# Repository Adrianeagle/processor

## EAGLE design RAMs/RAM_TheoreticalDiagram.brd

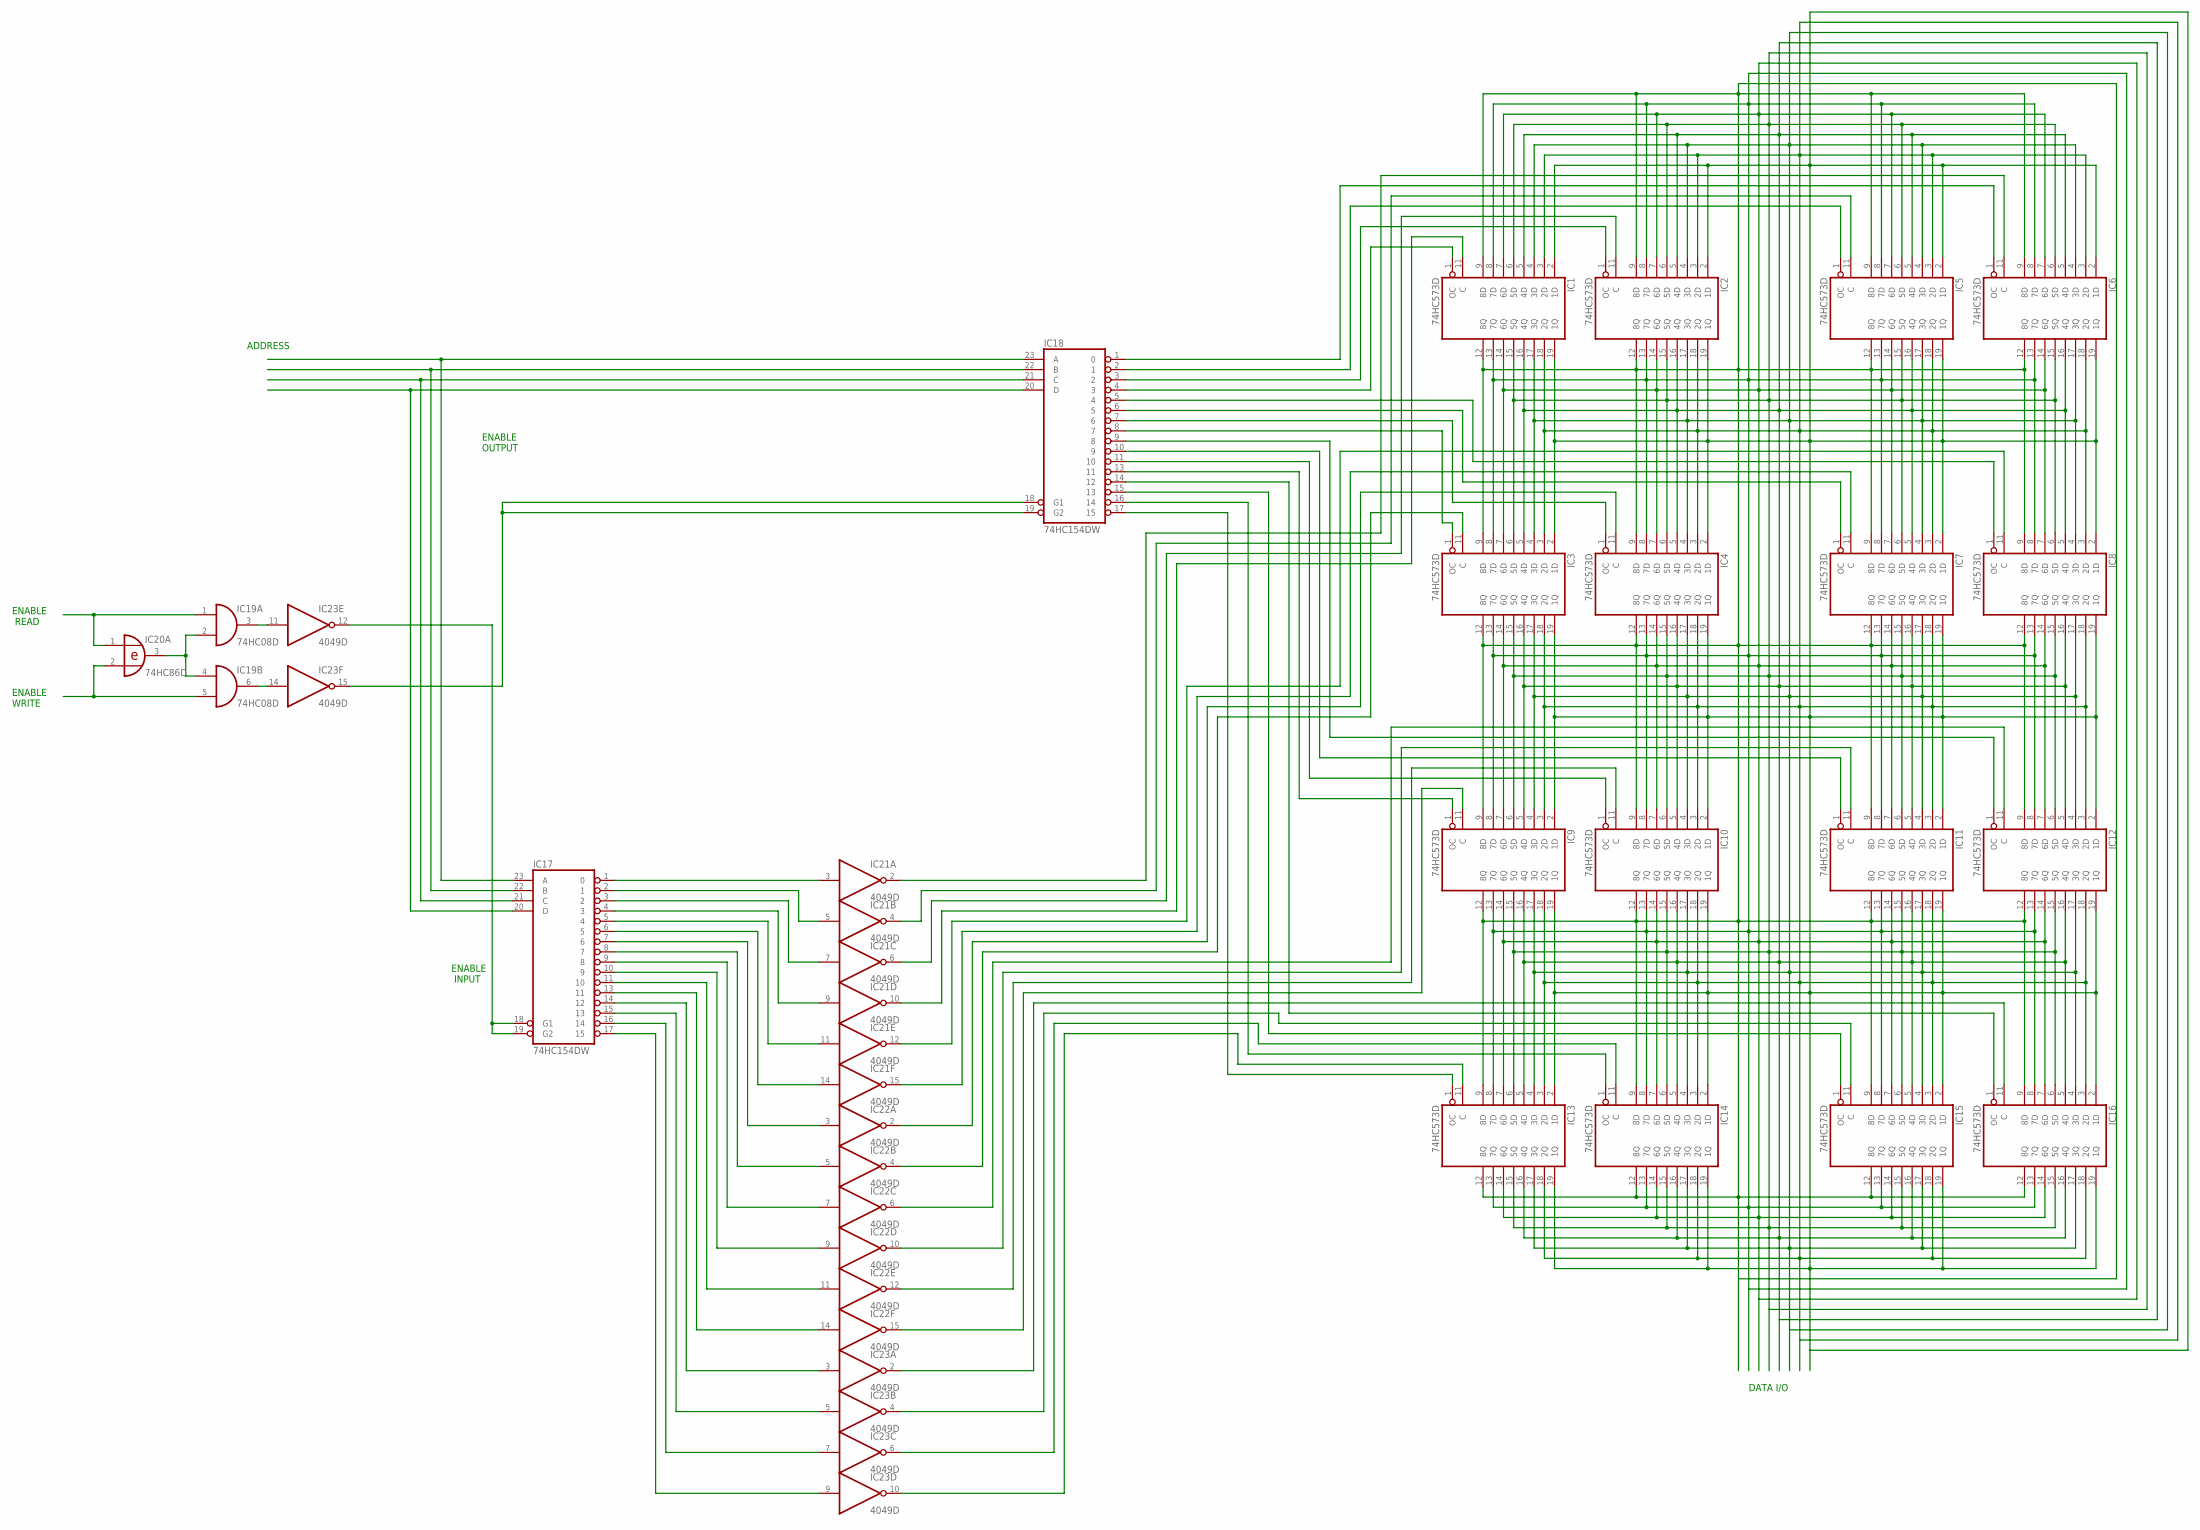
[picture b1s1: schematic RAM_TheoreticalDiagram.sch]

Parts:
IC1, IC2, IC3, IC4, IC5, IC6, IC7, IC8, IC9, IC10, IC11, IC12, IC13, IC14, IC15, IC16: 74HC573D; SO20W
IC17, IC18: 74HC154DW; SO24W
IC19: 74HC08D; SO14
IC20: 74HC86D; SO14
IC21, IC22, IC23: 4049D; SO16

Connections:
unnamed: IC16.11 (C), IC23.2 (O)
unnamed: IC16.1 (OC), IC18.14 (12)
unnamed: IC15.11 (C), IC23.4 (O)
unnamed: IC15.1 (OC), IC18.15 (13)
unnamed: IC14.11 (C), IC23.6 (O)
unnamed: IC14.1 (OC), IC18.16 (14)
unnamed: IC13.11 (C), IC23.10 (O)
unnamed: IC13.1 (OC), IC18.17 (15)
unnamed: IC12.11 (C), IC22.6 (O)
unnamed: IC1.9 (8D), IC1.12 (8Q), IC2.9 (8D), IC2.12 (8Q), IC3.9 (8D), IC3.12 (8Q), IC4.9 (8D), IC4.12 (8Q), IC5.9 (8D), IC5.12 (8Q), IC6.9 (8D), IC6.12 (8Q), IC7.9 (8D), IC7.12 (8Q), IC8.9 (8D), IC8.12 (8Q), IC9.9 (8D), IC9.12 (8Q), IC10.9 (8D), IC10.12 (8Q), IC11.9 (8D), IC11.12 (8Q), IC12.9 (8D), IC12.12 (8Q), IC13.9 (8D), IC13.12 (8Q), IC14.9 (8D), IC14.12 (8Q), IC15.9 (8D), IC15.12 (8Q), IC16.9 (8D), IC16.12 (8Q)
unnamed: IC1.8 (7D), IC1.13 (7Q), IC2.8 (7D), IC2.13 (7Q), IC3.8 (7D), IC3.13 (7Q), IC4.8 (7D), IC4.13 (7Q), IC5.8 (7D), IC5.13 (7Q), IC6.8 (7D), IC6.13 (7Q), IC7.8 (7D), IC7.13 (7Q), IC8.8 (7D), IC8.13 (7Q), IC9.8 (7D), IC9.13 (7Q), IC10.8 (7D), IC10.13 (7Q), IC11.8 (7D), IC11.13 (7Q), IC12.8 (7D), IC12.13 (7Q), IC13.8 (7D), IC13.13 (7Q), IC14.8 (7D), IC14.13 (7Q), IC15.8 (7D), IC15.13 (7Q), IC16.8 (7D), IC16.13 (7Q)
unnamed: IC12.1 (OC), IC18.9 (8)
unnamed: IC10.11 (C), IC22.12 (O)
unnamed: IC11.11 (C), IC22.10 (O)
unnamed: IC11.1 (OC), IC18.10 (9)
unnamed: IC10.1 (OC), IC18.11 (10)
unnamed: IC9.11 (C), IC22.15 (O)
unnamed: IC9.1 (OC), IC18.13 (11)
unnamed: IC8.1 (OC), IC18.5 (4)
unnamed: IC19.2 (I1), IC19.4 (I0), IC20.3 (O)
unnamed: IC8.11 (C), IC21.12 (O)
unnamed: IC7.11 (C), IC21.15 (O)
unnamed: IC7.1 (OC), IC18.6 (5)
unnamed: IC1.5 (4D), IC1.16 (4Q), IC2.5 (4D), IC2.16 (4Q), IC3.5 (4D), IC3.16 (4Q), IC4.5 (4D), IC4.16 (4Q), IC5.5 (4D), IC5.16 (4Q), IC6.5 (4D), IC6.16 (4Q), IC7.5 (4D), IC7.16 (4Q), IC8.5 (4D), IC8.16 (4Q), IC9.5 (4D), IC9.16 (4Q), IC10.5 (4D), IC10.16 (4Q), IC11.5 (4D), IC11.16 (4Q), IC12.5 (4D), IC12.16 (4Q), IC13.5 (4D), IC13.16 (4Q), IC14.5 (4D), IC14.16 (4Q), IC15.5 (4D), IC15.16 (4Q), IC16.5 (4D), IC16.16 (4Q)
unnamed: IC19.1 (I0), IC20.1 (I0)
unnamed: IC4.11 (C), IC22.2 (O)
unnamed: IC4.1 (OC), IC18.7 (6)
unnamed: IC3.11 (C), IC22.4 (O)
unnamed: IC1.3 (2D), IC1.18 (2Q), IC2.3 (2D), IC2.18 (2Q), IC3.3 (2D), IC3.18 (2Q), IC4.3 (2D), IC4.18 (2Q), IC5.3 (2D), IC5.18 (2Q), IC6.3 (2D), IC6.18 (2Q), IC7.3 (2D), IC7.18 (2Q), IC8.3 (2D), IC8.18 (2Q), IC9.3 (2D), IC9.18 (2Q), IC10.3 (2D), IC10.18 (2Q), IC11.3 (2D), IC11.18 (2Q), IC12.3 (2D), IC12.18 (2Q), IC13.3 (2D), IC13.18 (2Q), IC14.3 (2D), IC14.18 (2Q), IC15.3 (2D), IC15.18 (2Q), IC16.3 (2D), IC16.18 (2Q)
unnamed: IC3.1 (OC), IC18.8 (7)
unnamed: IC6.11 (C), IC21.2 (O)
unnamed: IC6.1 (OC), IC18.1 (0)
unnamed: IC5.11 (C), IC21.4 (O)
unnamed: IC5.1 (OC), IC18.2 (1)
unnamed: IC2.11 (C), IC21.6 (O)
unnamed: IC2.1 (OC), IC18.3 (2)
unnamed: IC1.11 (C), IC21.10 (O)
unnamed: IC1.1 (OC), IC18.4 (3)
unnamed: IC18.18 (G1), IC18.19 (G2), IC23.15 (O)
unnamed: IC17.18 (G1), IC17.19 (G2), IC23.12 (O)
unnamed: IC19.5 (I1), IC20.2 (I1)
unnamed: IC17.1 (0), IC21.3 (I)
unnamed: IC17.23 (A), IC18.23 (A)
unnamed: IC17.22 (B), IC18.22 (B)
unnamed: IC17.21 (C), IC18.21 (C)
unnamed: IC17.20 (D), IC18.20 (D)
unnamed: IC17.2 (1), IC21.5 (I)
unnamed: IC17.3 (2), IC21.7 (I)
unnamed: IC17.4 (3), IC21.9 (I)
unnamed: IC17.5 (4), IC21.11 (I)
unnamed: IC17.6 (5), IC21.14 (I)
unnamed: IC17.7 (6), IC22.3 (I)
unnamed: IC17.8 (7), IC22.5 (I)
unnamed: IC17.9 (8), IC22.7 (I)
unnamed: IC17.10 (9), IC22.9 (I)
unnamed: IC17.11 (10), IC22.11 (I)
unnamed: IC17.13 (11), IC22.14 (I)
unnamed: IC17.14 (12), IC23.3 (I)
unnamed: IC17.15 (13), IC23.5 (I)
unnamed: IC17.16 (14), IC23.7 (I)
unnamed: IC17.17 (15), IC23.9 (I)
unnamed: IC1.7 (6D), IC1.14 (6Q), IC2.7 (6D), IC2.14 (6Q), IC3.7 (6D), IC3.14 (6Q), IC4.7 (6D), IC4.14 (6Q), IC5.7 (6D), IC5.14 (6Q), IC6.7 (6D), IC6.14 (6Q), IC7.7 (6D), IC7.14 (6Q), IC8.7 (6D), IC8.14 (6Q), IC9.7 (6D), IC9.14 (6Q), IC10.7 (6D), IC10.14 (6Q), IC11.7 (6D), IC11.14 (6Q), IC12.7 (6D), IC12.14 (6Q), IC13.7 (6D), IC13.14 (6Q), IC14.7 (6D), IC14.14 (6Q), IC15.7 (6D), IC15.14 (6Q), IC16.7 (6D), IC16.14 (6Q)
unnamed: IC19.3 (O), IC23.11 (I)
unnamed: IC19.6 (O), IC23.14 (I)
unnamed: IC1.2 (1D), IC1.19 (1Q), IC2.2 (1D), IC2.19 (1Q), IC3.2 (1D), IC3.19 (1Q), IC4.2 (1D), IC4.19 (1Q), IC5.2 (1D), IC5.19 (1Q), IC6.2 (1D), IC6.19 (1Q), IC7.2 (1D), IC7.19 (1Q), IC8.2 (1D), IC8.19 (1Q), IC9.2 (1D), IC9.19 (1Q), IC10.2 (1D), IC10.19 (1Q), IC11.2 (1D), IC11.19 (1Q), IC12.2 (1D), IC12.19 (1Q), IC13.2 (1D), IC13.19 (1Q), IC14.2 (1D), IC14.19 (1Q), IC15.2 (1D), IC15.19 (1Q), IC16.2 (1D), IC16.19 (1Q)
unnamed: IC1.4 (3D), IC1.17 (3Q), IC2.4 (3D), IC2.17 (3Q), IC3.4 (3D), IC3.17 (3Q), IC4.4 (3D), IC4.17 (3Q), IC5.4 (3D), IC5.17 (3Q), IC6.4 (3D), IC6.17 (3Q), IC7.4 (3D), IC7.17 (3Q), IC8.4 (3D), IC8.17 (3Q), IC9.4 (3D), IC9.17 (3Q), IC10.4 (3D), IC10.17 (3Q), IC11.4 (3D), IC11.17 (3Q), IC12.4 (3D), IC12.17 (3Q), IC13.4 (3D), IC13.17 (3Q), IC14.4 (3D), IC14.17 (3Q), IC15.4 (3D), IC15.17 (3Q), IC16.4 (3D), IC16.17 (3Q)
unnamed: IC1.10 (GND), IC2.10 (GND), IC3.10 (GND), IC4.10 (GND), IC5.10 (GND), IC6.10 (GND), IC7.10 (GND), IC8.10 (GND), IC9.10 (GND), IC10.10 (GND), IC11.10 (GND), IC12.10 (GND), IC13.10 (GND), IC14.10 (GND), IC15.10 (GND), IC16.10 (GND), IC17.12 (GND), IC18.12 (GND), IC19.7 (GND), IC20.7 (GND)
unnamed: IC1.6 (5D), IC1.15 (5Q), IC2.6 (5D), IC2.15 (5Q), IC3.6 (5D), IC3.15 (5Q), IC4.6 (5D), IC4.15 (5Q), IC5.6 (5D), IC5.15 (5Q), IC6.6 (5D), IC6.15 (5Q), IC7.6 (5D), IC7.15 (5Q), IC8.6 (5D), IC8.15 (5Q), IC9.6 (5D), IC9.15 (5Q), IC10.6 (5D), IC10.15 (5Q), IC11.6 (5D), IC11.15 (5Q), IC12.6 (5D), IC12.15 (5Q), IC13.6 (5D), IC13.15 (5Q), IC14.6 (5D), IC14.15 (5Q), IC15.6 (5D), IC15.15 (5Q), IC16.6 (5D), IC16.15 (5Q)
unnamed: IC1.20 (VCC), IC2.20 (VCC), IC3.20 (VCC), IC4.20 (VCC), IC5.20 (VCC), IC6.20 (VCC), IC7.20 (VCC), IC8.20 (VCC), IC9.20 (VCC), IC10.20 (VCC), IC11.20 (VCC), IC12.20 (VCC), IC13.20 (VCC), IC14.20 (VCC), IC15.20 (VCC), IC16.20 (VCC), IC17.24 (VCC), IC18.24 (VCC), IC19.14 (VCC), IC20.14 (VCC)
VDD: IC21.1 (VDD), IC22.1 (VDD), IC23.1 (VDD)
VSS: IC21.8 (VSS), IC22.8 (VSS), IC23.8 (VSS)

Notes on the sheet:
ENABLE OUTPUT
ENABLE INPUT
ADDRESS
ENABLE READ
ENABLE WRITE
DATA I/O

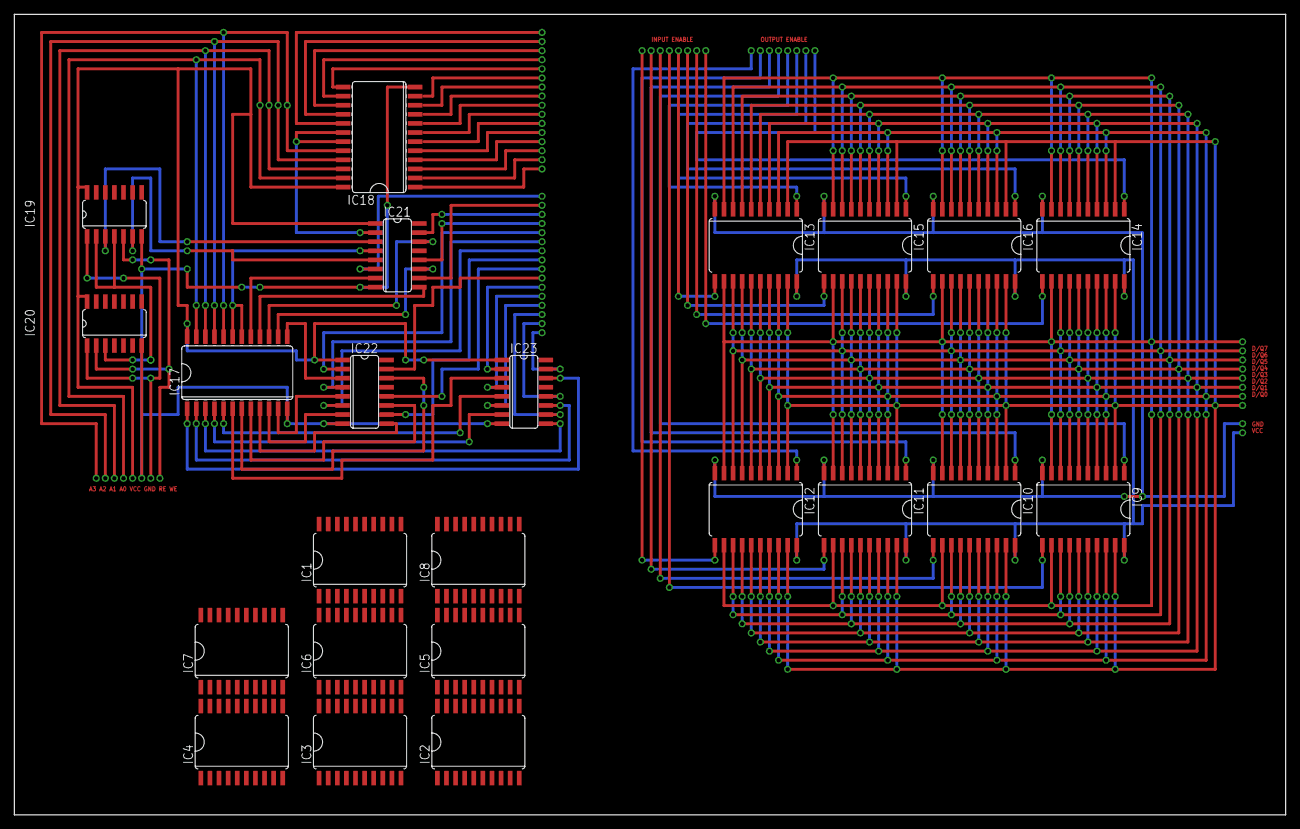
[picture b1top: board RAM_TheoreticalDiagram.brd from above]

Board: 2 copper layers, 177.5 x 111.8 mm, 23 parts (0 on the bottom side), 71 nets.

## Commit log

2017-08-23 Created diagram for the processor RAMs
2017-08-23 Added the ALU Diagram
2017-08-23 ALU diagram + actual board
2017-08-23 Switched to SN74LS283D Adder
2017-08-23 Added some routes
2017-08-23 Finished the ALU diagram
2017-08-26 Finished the Read/Write Verification
2017-08-26 Added the RAM board image
2017-08-26 Finished the RAM boards
2017-08-26 Changed the dimension of the board a bit
2017-08-26 Saved a new board image
2017-08-26 Added the existing components datasheets
2017-09-03 Added the simulation in Proteus
